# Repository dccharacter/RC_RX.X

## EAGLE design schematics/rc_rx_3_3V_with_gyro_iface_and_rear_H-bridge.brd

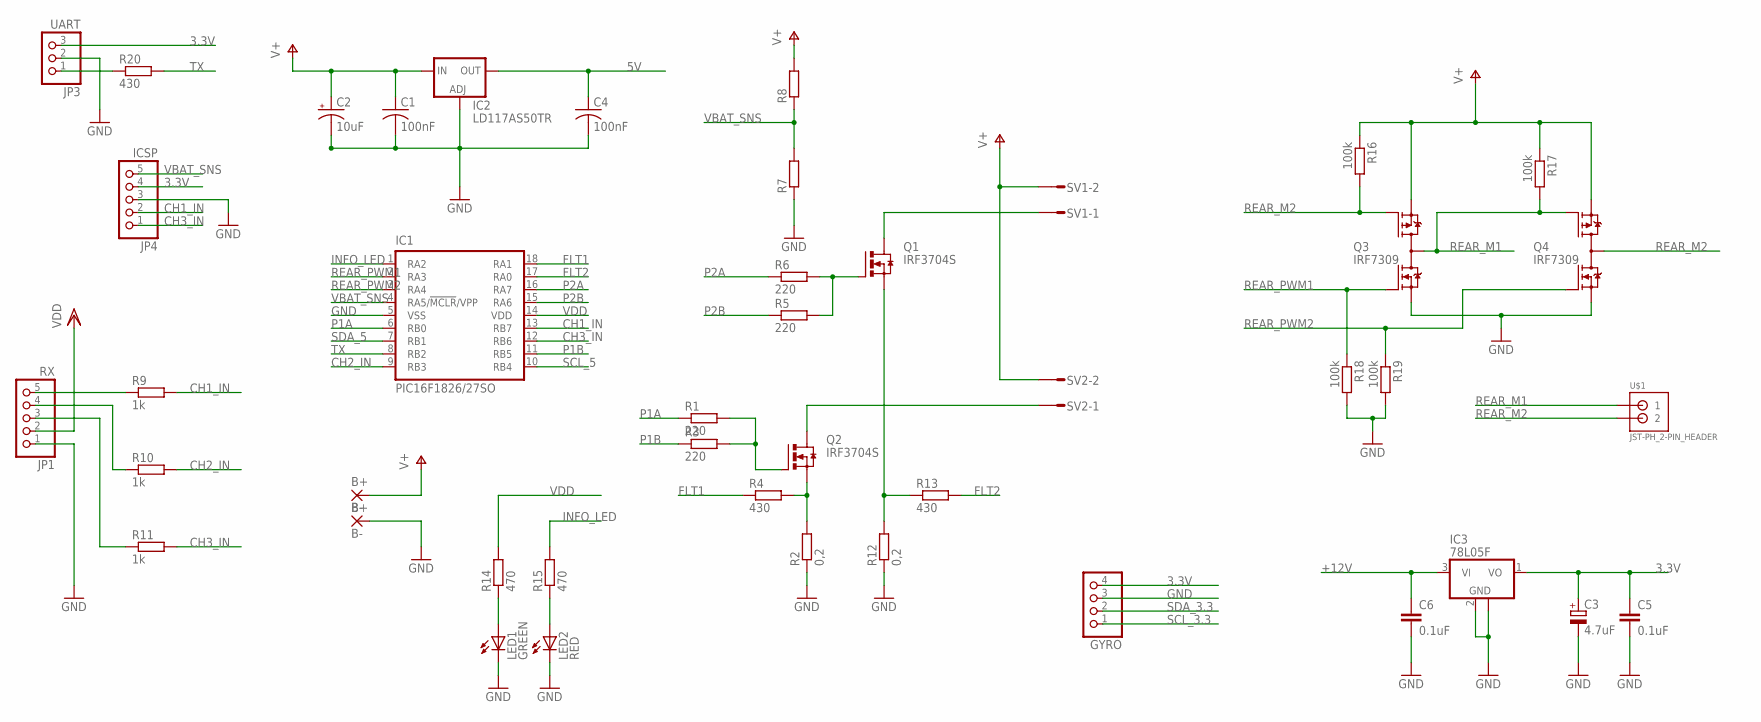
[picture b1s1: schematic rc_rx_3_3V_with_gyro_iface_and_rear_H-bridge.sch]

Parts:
B+: B+; 3,81/1,4
B-: B-; 3,81/1,4
C1, C4: 100nF; C0805
C2: 10uF; E3,5-8
C3: 4.7uF; E1,8-4
C5, C6: 0.1uF; C0805
GYRO: PINHD-1X4; 1X04
IC1: PIC16F1826/27SO; SO-18W
IC2: LD117AS50TR; SOT223
IC3: 78L05F; SOT89
JP1: RX; 1X05
JP3: UART; 1X03
JP4: ICSP; 1X05
LED1: GREEN; CHIP-LED0603
LED2: RED; CHIP-LED0603
Q1, Q2: IRF3704S; D2PACK
Q3, Q4: IRF7309; SO08-IRF
R1, R3, R6: 220; M0805
R2, R12: 0,2; M0805
R4, R13, R20: 430; M0805
R5: 220; R0805
R7, R8: R-EU_R0805; R0805
R9, R10, R11: 1k; M0805
R14, R15: 470; M0805
R16, R17, R18, R19: 100k; M0805
SV1, SV2: S02P
U$1: JST-PH_2-PIN_HEADER; JST_B2B-PH_HEADER

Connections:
3.3V: C3.+, C5.1, GYRO.4, IC3.1 (VO), JP3.3, JP4.4
5V: C4.1, IC2.4 (OUT)
+12V: C6.1, IC3.3 (VI)
CH1_IN: IC1.13 (RB7), JP4.2, R9.2
CH2_IN: IC1.9 (RB3), R10.2
CH3_IN: IC1.12 (RB6), JP4.1, R11.2
CRR_SNS: Q1.3 (S), R12.2, R13.1
FLT1: IC1.18 (RA1), R4.1
FLT2: IC1.17 (RA0), R13.2
GND: B-.1, C1.2, C2.-, C3.-, C4.2, C5.2, C6.2, GYRO.3, IC1.5 (VSS), IC2.1 (ADJ), IC3.2 (GND), IC3.2@1 (GND), JP1.1, JP3.2, JP4.3, LED1.C, LED2.C, Q3.1 (N-S), Q4.1 (N-S), R2.1, R7.1, R12.1, R18.2, R19.2
INFO_LED: IC1.1 (RA2), R15.2
unnamed: Q2.1 (G), R1.2, R3.2
unnamed: Q1.1 (G), R5.2, R6.2
unnamed: Q2.2 (D), SV2.1
unnamed: Q1.2 (D), SV1.1
unnamed: JP1.5, R9.1
unnamed: JP1.4, R10.1
unnamed: JP1.3, R11.1
unnamed: Q2.3 (S), R2.2, R4.2
unnamed: LED1.A, R14.1
unnamed: LED2.A, R15.1
unnamed: JP3.1, R20.1
P1A: IC1.6 (RB0), R1.1
P1B: IC1.11 (RB5), R3.1
P2A: IC1.16 (RA7), R6.1
P2B: IC1.15 (RA6), R5.1
REAR_M1: Q3.5 (D), Q3.6 (D), Q3.7 (D), Q3.8 (D), Q4.4 (P-G), R17.2, U$1.P1 (1)
REAR_M2: Q3.4 (P-G), Q4.5 (D), Q4.6 (D), Q4.7 (D), Q4.8 (D), R16.2, U$1.P2 (2)
REAR_PWM1: IC1.2 (RA3), Q3.2 (N-G), R18.1
REAR_PWM2: IC1.3 (RA4), Q4.2 (N-G), R19.1
SCL_3.3: GYRO.1
SCL_5: IC1.10 (RB4)
SDA_3.3: GYRO.2
SDA_5: IC1.7 (RB1)
TX: IC1.8 (RB2), R20.2
V+: B+.1, C1.1, C2.+, IC2.3 (IN), Q3.3 (P-S), Q4.3 (P-S), R8.2, R16.1, R17.1, SV1.2, SV2.2
VBAT_SNS: IC1.4 (RA5/!MCLR!/VPP), JP4.5, R7.2, R8.1
VDD: IC1.14 (VDD), JP1.2, R14.2

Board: 2 copper layers, 44 parts (0 on the bottom side), 34 nets, no tracks yet.

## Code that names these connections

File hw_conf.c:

#include <xc.h>
#include <stdint.h>
#include "hw_conf.h"
#include "usart.h"

void hw_config(void)
{
    OSCCONbits.SPLLEN = 0;
    OSCCONbits.IRCF = OSC_SET;
    OSCCONbits.SCS = 0b10;

    OPTION_REGbits.nWPUEN = 0;

    OPTION_REGbits.T0CS = 0; // Fosc/4 clock
    OPTION_REGbits.PSA = 1; // PRESC is not assigned to TMR0, so it's 1:1
    //OPTION_REGbits.PS = 0b000; //1:2 PRESC

    while (!OSCSTATbits.HFIOFS); //wait for HFIO

    //Pins setup
    APFCON0 = 0b00011001;
    APFCON1 = 0b0;

    ANSELA = 0;
    ANSELB = 0;

    TRISB = 0b11111011;
    TRISA = 0b11111111;

    WPUB = 0b00011010; //RB1,3,4

    //USART setup

    SPBRGH = SPBRGH_CALC;//0;
    SPBRGL = SPBRGL_CALC;//16;
    BRGH = 1;
    BRG16 = 1;
    SYNC = 0;
    TXEN = 1;
    CREN = 1;
    SPEN = 1;
    //RCIE = 1;
    RCIF = 0;
    
    /* FVR config
     */
    FVRCONbits.CDAFVR = 0b01; // 01 = 1.024V, 10 = 2.048
    FVRCONbits.ADFVR = 0b01; // 1.024V
    FVRCONbits.FVREN = 1;
    while (!FVRCONbits.FVRRDY); // Wait till FVR is ready to use

    /* Comparator config
     * Negative input is signal
     * Positive input is Vref = 1.024V
     * With shunt resistors = 0.2 Ohm, shutdown will occure when current exceeds 5A
     * Inputs on RA2 and RA3
     * RA2 - channel PX, C12IN2-
     * RA3 - channel PX, C12IN3-
     */
    CM1CON1bits.C1PCH = 0b10; // Connected to FVR
    CM1CON1bits.C1NCH = 0b10; // Connected to C12IN2-, i.e. RA2
    CM1CON0bits.C1POL = 1; // 1 = inverted polarity
    CM1CON0bits.C1ON = 1;

    CM2CON1bits.C2PCH = 0b10; // Connected to FVR
    CM2CON1bits.C2NCH = 0b11; // Connected to C12IN3-, i.e. RA3
    CM2CON0bits.C2POL = 1; // 1 = inverted polarity
    CM2CON0bits.C2ON = 1;


    /* PWM config
     * Two channels ECCP, each channel is driven with two pins (e.g. P1A-P1B and P2A-P2B
     * A and B work in the same phase, just to multiply current that builds boltage on FET gate
     * Auto-shutdown is enabled, driven by comparator
     * Either comparator event would disable both P1 and P2 channels
     * No auto-resume is set
     */
   
    CCP1CON = 0b10001101;
    CCP2CON = 0b10001101;

    CCP1ASbits.CCP1AS = 0;//0b011; //eithe comparator 1 or 2 is high
    CCP1ASbits.PSS1AC = 0;
    CCP1ASbits.PSS1BD = 0;
    PWM1CONbits.P1RSEN = 1; // 0 - no autorestart
    CCP2ASbits.CCP2AS = 0;//0b011; //eithe comparator 1 or 2 is high
    CCP2ASbits.PSS2AC = 0;
    CCP2ASbits.PSS2BD = 0;
    PWM2CONbits.P2RSEN = 1; // 0 - no autorestart

#ifdef PWM_DRV_CTRL
    PR2 = TMR_PR_SET;
    PR4 = TMR_PR_SET;

    CCPR1L = 0;
    CCPR2L = 0;

    CCPTMRSbits.C1TSEL = 0; // CCP1 is on TMR2
    CCPTMRSbits.C2TSEL = 1; // CCP2 is on TMR4

    T2CONbits.T2CKPS = TMR_PRESC_SET;
    T4CONbits.T4CKPS = TMR_PRESC_SET;

    TMR2ON = 1;
    TMR4ON = 1;

#endif //#ifdef PWM_DRV_CTRL

    TRISB0 = 0; //P1A
    TRISB5 = 0; //P2B
    
    TRISA7 = 0; //P2A
    TRISA6 = 0; //P2B

    /* RB1 -
     * RB3 -
     * RB4 -
     */
    IOCBP = 0b00011010;
    IOCBN = 0b00011010;
    IOCIE = 1;
    PEIE = 1;
    

    T1CON = 0b00000001;

    ANSA4 = 1;
    ADCON1bits.ADFM = 1; // 1 = right justified
    ADCON1bits.ADCS = 0b101; // 1 = Fosc/8; 010 = Fosc/32; 101 = Fosc/16
    ADCON1bits.ADNREF = 0; // VSS
    ADCON1bits.ADPREF = 0b11; // FVR
    ADCON0 =  0b00010011;
    ADIF = 0;
    ADIE = 1;

    TRISB6 = 0; // LED
    RB6 = 0;

    GIE = 1;
}

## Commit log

2014-07-21 First flying version
2014-07-21 Added schematics
2014-07-23 Fail-safe and proper steering
2014-07-26 Proper proper yaw
    Yaw is compensated for heavy fly bar
    yaw input is filtered
    Proper (and filtered) battery voltage reading
2014-07-27 Added schematics for 3-3V with rear rotor and gyro
2014-08-08 Working on broken ADC and MSSP
    This commit is to show to Microchip
2014-08-09 Redid i2c functions
    In vain though
2014-08-13 PID coeffs can now be set remotely
    by sending four-byte command
    first byte is a symbol i or p or d
    second and third - 16 bit value
    and then p to close the packet
2014-08-14 broke everything
2014-08-14 github asks
2014-08-14 conflict
2014-08-14 Revert "Redid i2c functions"
    This reverts commit 38c9c01b75cd938198a7ec9c6ea9bed839b5eb4e.
    Conflicts:
    hw_conf_v1.c
    i2c.c
    main.c
2014-08-14 DND - Trying to recover info commit
    I have a conflict that I need to resolve. This code works.
